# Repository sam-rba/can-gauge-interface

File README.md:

# Analog Gauge Driver with CAN Interface

Automotive electronic device that drives up to six analog gauges using data from a CAN bus.

## Contents

- `hw/` — Hardware; KiCad files for the PCB.
- `fw/` — Firmare that runs on the PIC microcontroller.
- `sw/` — Software for flashing calibration files onto the device.
- `doc/` — Documentation.

## Features

### Interfaces
- CAN 2.0B interface, up to 500kbps
- Flexible CAN encoding scheme, configurable via CAN

### Outputs
- 1 tachometer output
- 1 speedometer output
- 4 analog outputs (0–5V)

### Power supply
- 9–16V DC input

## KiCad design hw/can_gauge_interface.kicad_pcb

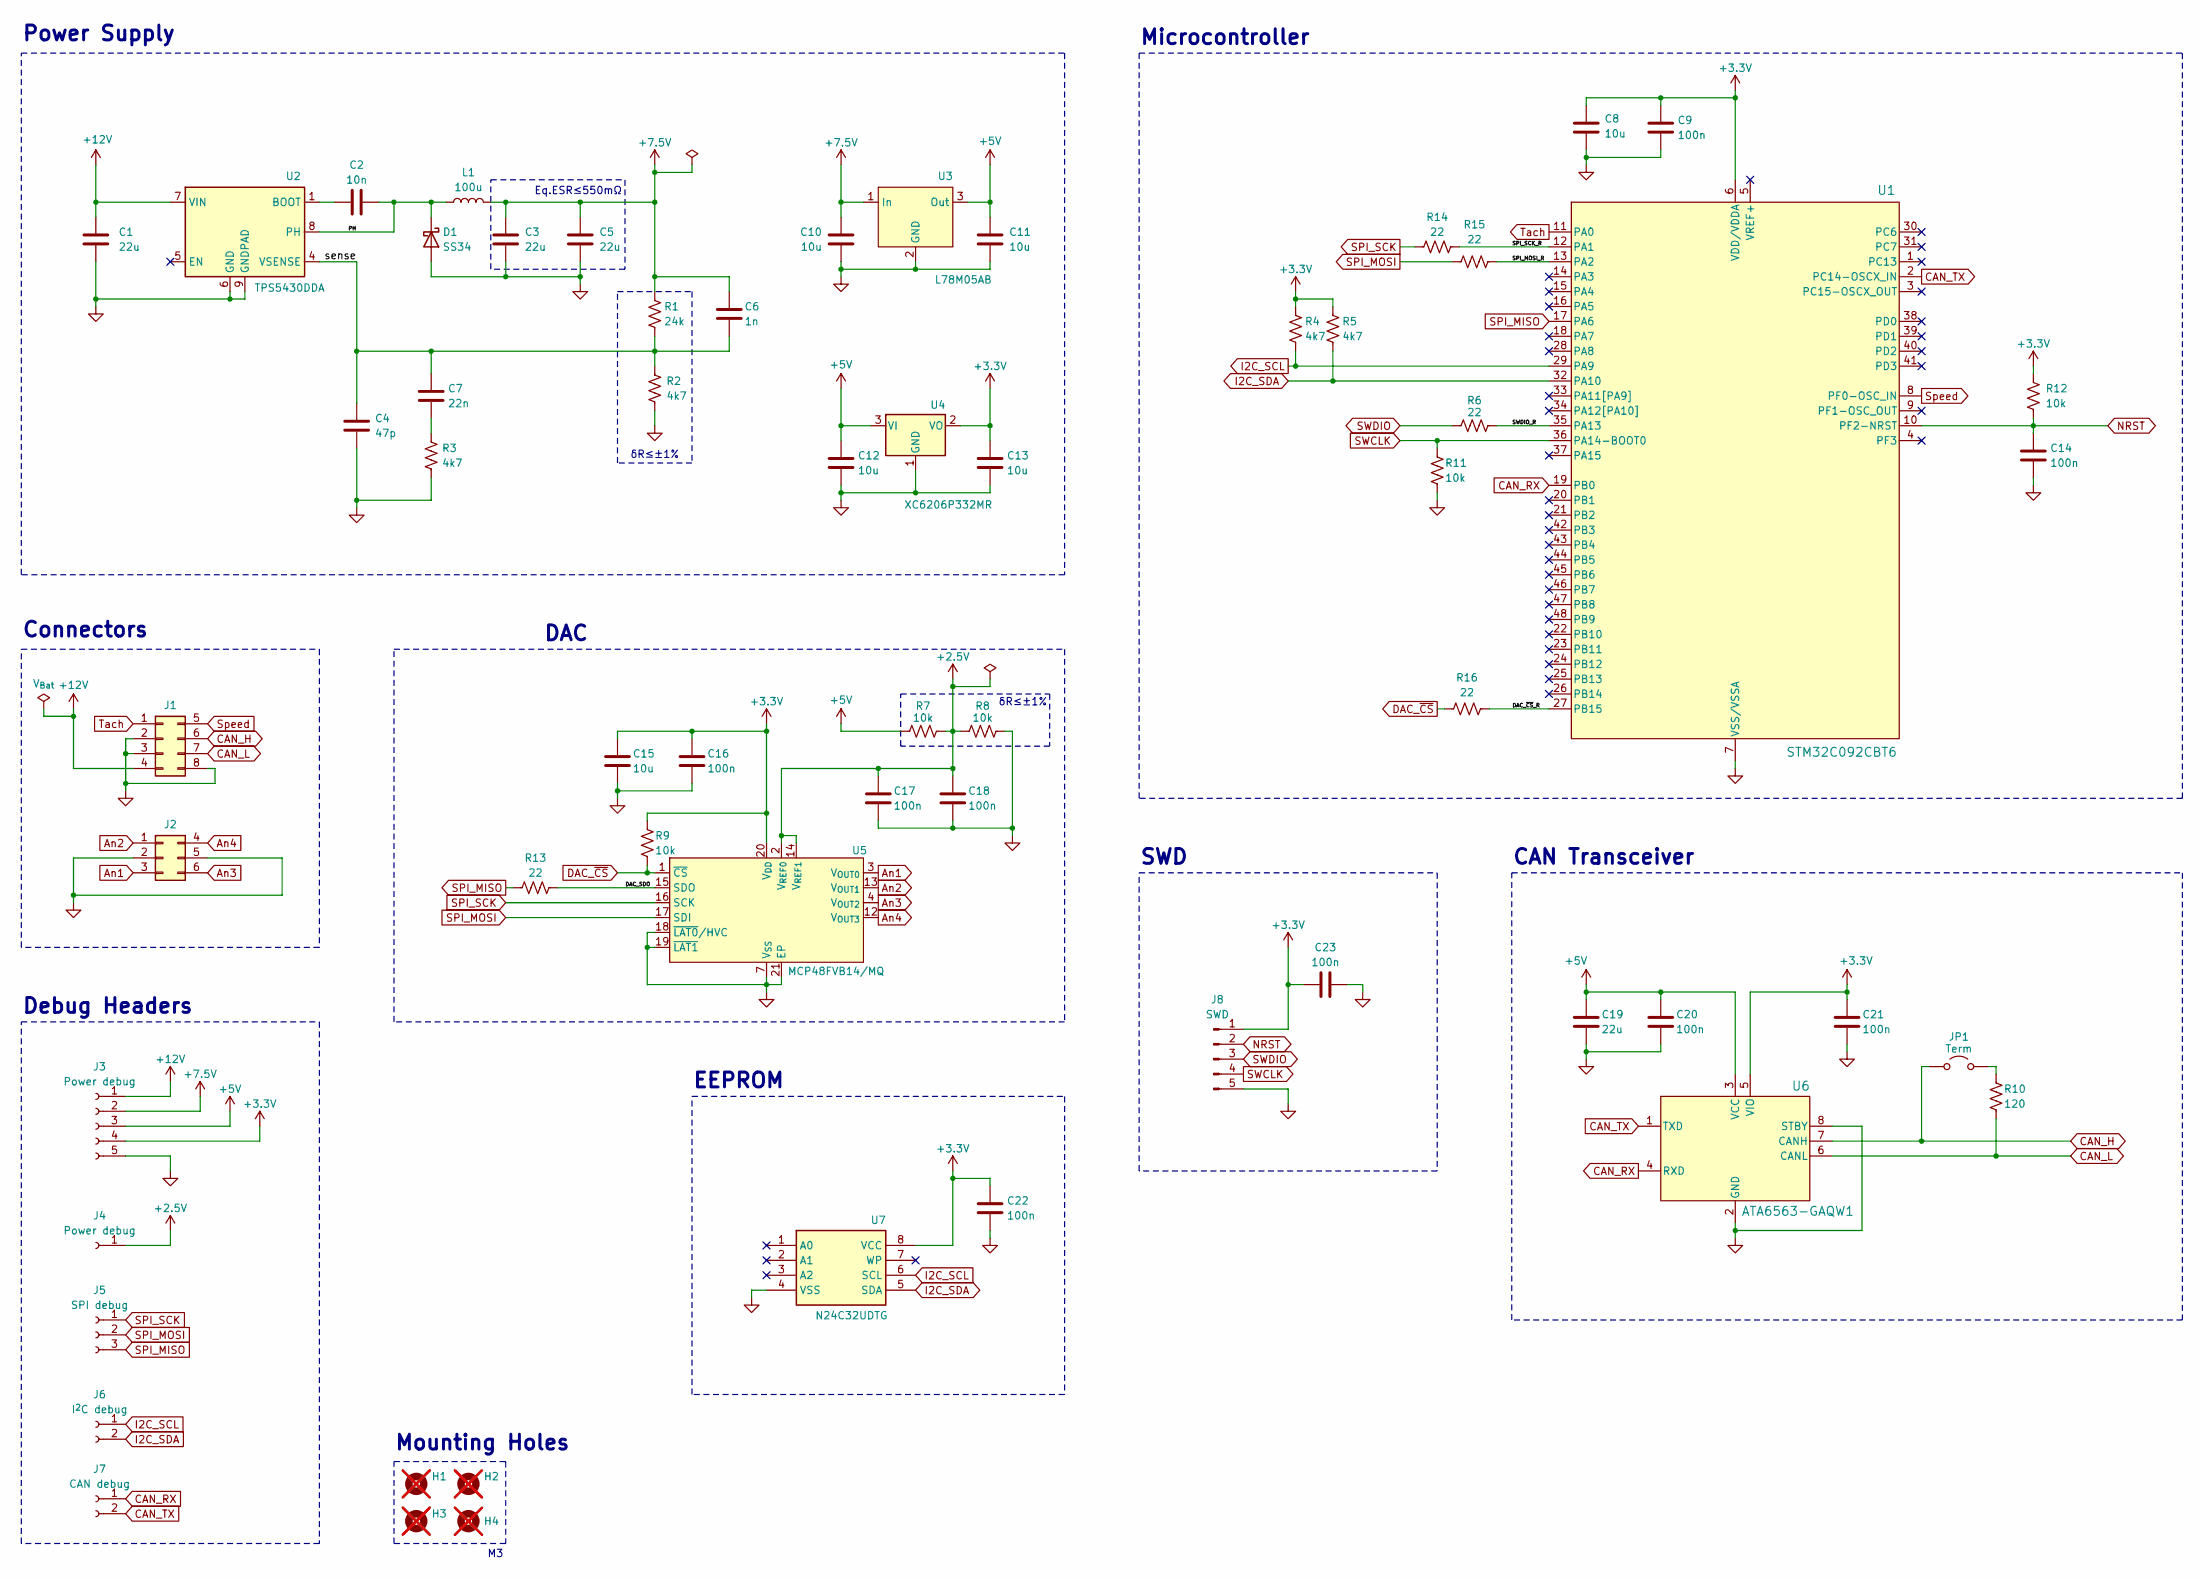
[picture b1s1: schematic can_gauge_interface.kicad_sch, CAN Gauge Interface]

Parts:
C1, C3, C5, C19: 22u; C_1206_3216Metric
C2: 10n; C_0402_1005Metric
C4: 47p; C_0402_1005Metric
C6: 1n; C_0603_1608Metric
C7: 22n; C_0603_1608Metric
C8, C10, C11, C12, C13, C15: 10u; C_0805_2012Metric
C9, C14, C16, C17, C18, C20, C21, C22, C23: 100n; C_0402_1005Metric
D1: SS34; D_SMA
H1, H2, H3, H4: MountingHole; MountingHole_3.2mm_M3_DIN965; not fitted
J1: Conn_02x04_Top_Bottom; Molex_Mini-Fit_Jr_5569-08A2_2x04_P4.20mm_Horizontal
J2: Analog; Molex_Mini-Fit_Jr_5569-06A2_2x03_P4.20mm_Horizontal
J3: Power debug; PinSocket_1x05_P2.54mm_Vertical
J4: Power debug; PinSocket_1x01_P2.54mm_Vertical
J5: SPI debug; PinSocket_1x03_P2.54mm_Vertical
J6: I^{2}C debug; PinSocket_1x02_P2.54mm_Vertical
J7: CAN debug; PinSocket_1x02_P2.54mm_Vertical
J8: SWD; PinHeader_1x05_P2.54mm_Vertical
JP1: Term; TestPoint_2Pads_Pitch2.54mm_Drill0.8mm
L1: 100u; L_TaiTech_TMPC1265_13.5x12.5mm
R1: 24k; R_0603_1608Metric
R2, R3, R4, R5: 4k7; R_0603_1608Metric
R6, R13, R14, R15, R16: 22; R_0603_1608Metric
R7, R8, R9, R11, R12: 10k; R_0603_1608Metric
R10: 120; R_0603_1608Metric
U1: STM32C092CBT6; LQFP48_STM
U2: TPS5430DDA; TI_SO-PowerPAD-8
U3: L78M05AB; TO-252-2
U4: XC6206P332MR; SOT-23-3
U5: MCP48FVB14/MQ; Texas_RGW0020A_VQFN-20-1EP_5x5mm_P0.65mm_EP3.15x3.15mm
U6: ATA6563-GAQW1; SOIC8_SN_MCH
U7: N24C32UDTG; SOP50P312X90-8N; Manufacturer_Part_Number N24C32UDTG; Mouser Part Number 863-N24C32UDTG

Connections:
+2.5V: C17.1, C18.1, J4.1, R7.2, R8.1, U5.2 (V_{REF0}), U5.14 (V_{REF1})
+3.3V: C8.1, C9.1, C13.1, C15.1, C16.1, C21.1, C22.1, C23.1, J3.4, J8.1, R4.1, R5.1, R9.1, R12.1, U1.6 (VDD/VDDA), U4.2 (VO), U5.20 (V_{DD}), U6.5 (VIO), U7.8 (VCC)
+5V: C11.1, C12.1, C19.1, C20.1, J3.3, R7.1, U3.3 (Out), U4.3 (VI), U6.3 (VCC)
+7.5V: C3.1, C5.1, C6.1, C10.1, J3.2, L1.2, R1.1, U3.1 (In)
+12V: C1.1, J1.4, J3.1, U2.7 (VIN)
/DAC_SDO: R13.2, U5.15 (SDO)
/DAC_~CS_R: R16.2, U1.27 (PB15)
/PH: C2.2, D1.1 (K), L1.1, U2.8 (PH)
/SPI_MOSI_R: R15.2, U1.13 (PA2)
/SPI_SCK_R: R14.2, U1.12 (PA1)
/SWDIO_R: R6.2, U1.35 (PA13)
/sense: C4.1, C6.2, C7.1, R1.2, R2.1, U2.4 (VSENSE)
An1: J2.3, U5.3 (V_{OUT0})
An2: J2.1, U5.13 (V_{OUT1})
An3: J2.6, U5.4 (V_{OUT2})
An4: J2.4, U5.12 (V_{OUT3})
CAN_H: J1.6, JP1.1 (A), U6.7 (CANH)
CAN_L: J1.7, R10.2, U6.6 (CANL)
CAN_RX: J7.1, U1.19 (PB0), U6.4 (RXD)
CAN_TX: J7.2, U1.2 (PC14-OSCX_IN), U6.1 (TXD)
DAC_~CS: R9.2, R16.1, U5.1 (~CS)
GND: C1.2, C3.2, C4.2, C5.2, C8.2, C9.2, C10.2, C11.2, C12.2, C13.2, C14.2, C15.2, C16.2, C17.2, C18.2, C19.2, C20.2, C21.2, C22.2, C23.2, D1.2 (A), J1.2, J1.3, J1.8, J2.2, J2.5, J3.5, J8.5, R2.2, R3.2, R8.2, R11.2, U1.7 (VSS/VSSA), U2.6 (GND), U2.9 (GNDPAD), U3.2 (GND), U4.1 (GND), U5.7 (V_{SS}), U5.18 (~LAT0/HVC), U5.19 (~LAT1), U5.21 (EP), U6.2 (GND), U6.8 (STBY), U7.4 (VSS)
I2C_SCL: J6.1, R4.2, U1.29 (PA9), U7.6 (SCL)
I2C_SDA: J6.2, R5.2, U1.32 (PA10), U7.5 (SDA)
NRST: C14.1, J8.2, R12.2, U1.10 (PF2-NRST)
unnamed: C7.2, R3.1
unnamed: JP1.2 (B), R10.1
unnamed: C2.1, U2.1 (BOOT)
SPI_MISO: J5.3, R13.1, U1.17 (PA6)
SPI_MOSI: J5.2, R15.1, U5.17 (SDI)
SPI_SCK: J5.1, R14.1, U5.16 (SCK)
SWCLK: J8.4, R11.1, U1.36 (PA14-BOOT0)
SWDIO: J8.3, R6.1
Speed: J1.5, U1.8 (PF0-OSC_IN)
Tach: J1.1, U1.11 (PA0)

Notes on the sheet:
Connectors
Microcontroller
Power Supply
Eq.ESR≤550mΩ
δR≤±1%
DAC
SWD
Mounting Holes
CAN Transceiver
Debug Headers
EEPROM

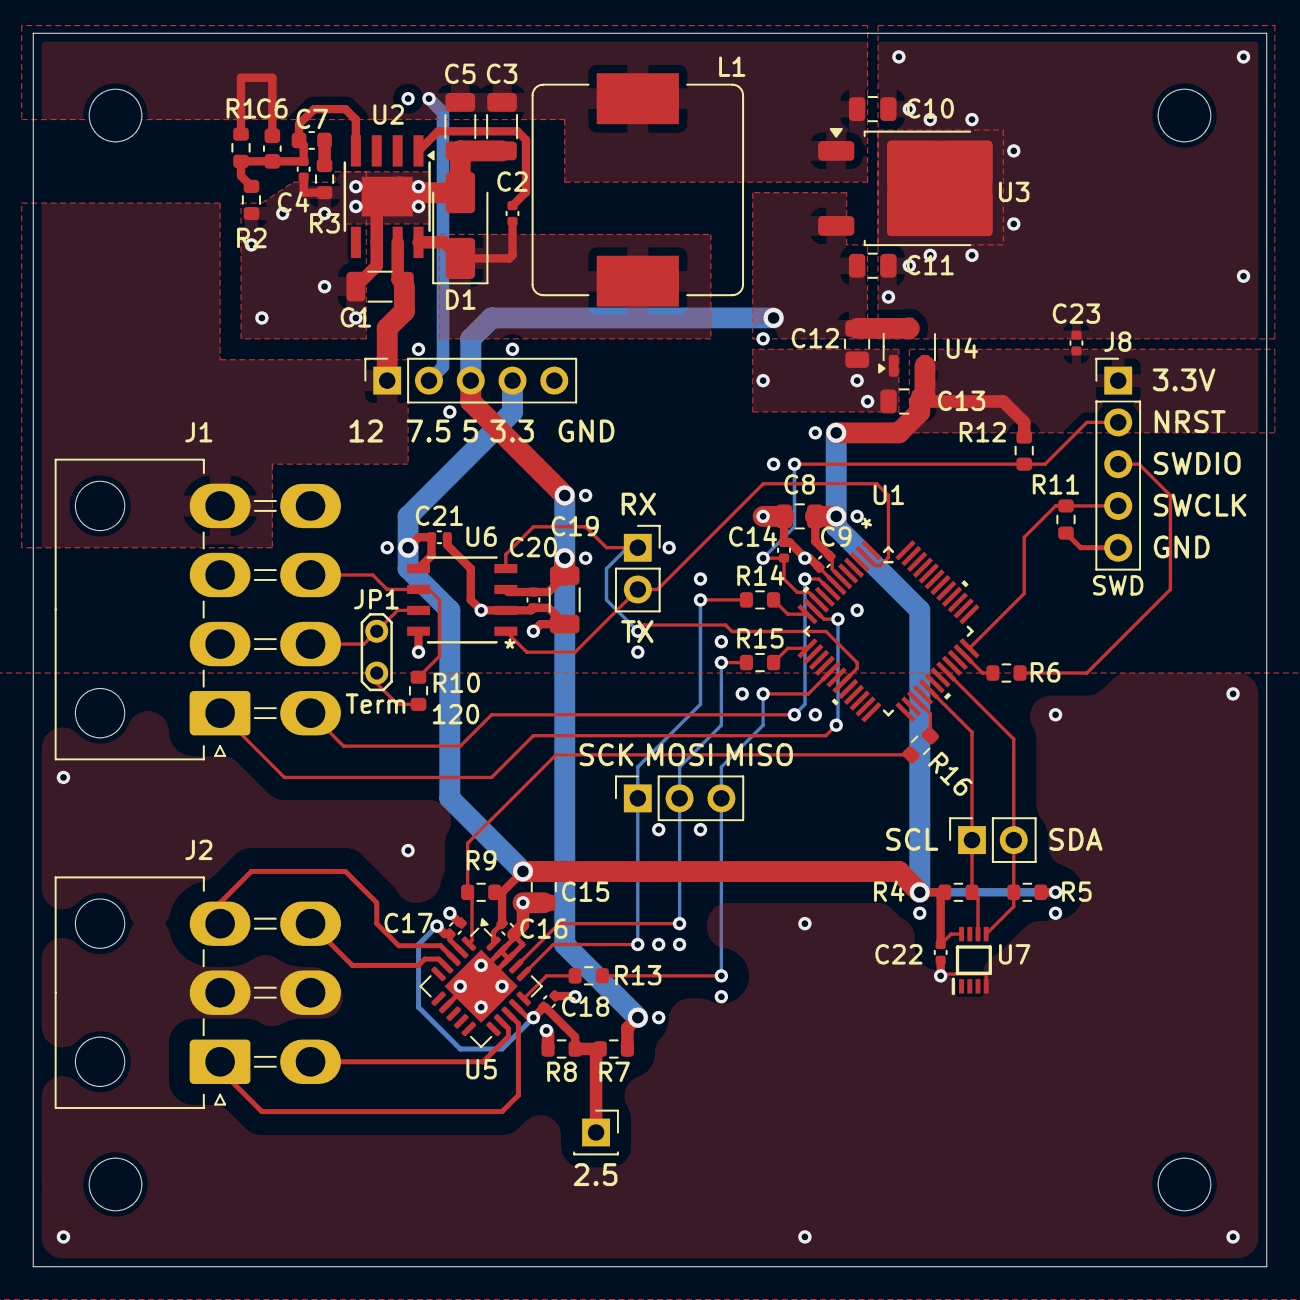
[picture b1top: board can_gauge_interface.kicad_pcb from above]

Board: 4 copper layers, 75.0 x 75.0 mm, 61 parts (0 on the bottom side), 35 nets.

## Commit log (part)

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2025-07-23 proposal
2025-07-24 spelling
2025-08-03 makefile and main.c
2025-08-14 usb protocol
2025-08-16 spi and eeprom modules
2025-08-16 add device and compiler to header comments
2025-08-16 add systests to makefile
2025-08-16 usbcom: modified libusb example
2025-08-16 clean up usbcom
2025-09-02 update proposal
2025-09-04 mla_usb submodule
2025-09-04 fw: usb
2025-09-05 debug usb
2025-09-05 rework usb state machine
2025-09-05 fix bug in usbcom
2025-09-05 usb: preemptive bug fix
2025-09-05 usb: add nack to protocol
2025-09-06 unity submodule
2025-09-06 usb getchar()
2025-09-06 fw: handle "w" write eeprom command
2025-09-06 fw: handle "r" eeprom read command
2025-09-06 make microchip source files non-executable
2025-09-06 tach/speedo discussion
2025-09-07 power budget
2025-09-07 power supply schematic
2025-09-07 schematic: MCLR, USB, ICSP
2025-09-07 schematic: EEPROM
2025-09-07 schematic: CAN
2025-09-08 schematic: connectors
2025-09-08 schematic: spi debug header
2025-09-08 more debug headers
2025-09-08 schematic: CAN termination jumper
2025-09-17 usbcom go rewrite
2025-09-17 usbcom refactor
2025-09-17 bug fix: eeprom usb newline
2025-09-19 hw: digital and analog LDOs
2025-09-19 hw: 6v6 debug pin
2025-09-19 hw: connected pic gpios
2025-09-19 hw: fixed erc warnings
2025-09-19 footprints
2025-09-20 buck converter layout and routing
2025-09-20 analog ldo layout and routing
2025-09-20 analog routing
2025-09-20 digital ldo layout and routing
2025-09-20 tht decoupling caps
2025-09-20 layout
2025-09-20 dac pullup layout
2025-09-20 4 layer stackup and CAN routing
2025-09-20 spi routing
2025-09-20 int pin routing
2025-09-20 CAN_CS routing
2025-09-20 icsp routing
2025-09-20 usb data routing
2025-09-20 speed and tach routing
2025-09-20 connected buck to conn pin
2025-09-20 dac spi routing
2025-09-20 move sck away from analog
2025-09-20 mounting hole placement
2025-09-20 edge cuts
2025-09-22 moved analog
2025-09-22 gnd vias
2025-09-22 drc warnings
2025-09-22 gnd pours
2025-09-27 psu ic 3d models
2025-09-27 tht quote
2025-09-27 schematic: tps5430 buck
2025-09-27 schematic: ldos
2025-09-27 schemtic: removed DNP flags
2025-09-27 wurth usb connector symbol
2025-09-27 board setup
2025-09-27 buck layout
2025-09-27 ldo layout
2025-09-27 can layout
2025-09-28 pic layout
2025-09-29 tht passives
2025-09-29 buck routing
2025-09-29 routing
2025-09-29 more routing
2025-09-29 wash
2025-10-01 tune usb trace length
2025-10-01 removed usb vbus
2025-10-01 manufacturing files
2025-10-01 connector 3d models
2025-10-02 manufacturing
2025-10-02 spi systest
2025-10-02 dac fw module
2025-10-03 CAN bit timing
2025-10-03 mcp2515 spi functions
2025-10-04 fix bug in bittiming script
2025-10-04 CAN filter- and mask-setting functions
2025-10-13 midterm report: intro and desiderata
2025-10-13 midterm report: component selection
2025-10-13 midterm report: pcb design
2025-10-13 midterm report: firmware
2025-10-13 midterm report: next steps
2025-10-13 midterm report: wash
2025-10-14 remove deprecated power supply doc
2025-10-14 remove old usbcom makefile
2025-10-14 reduce size of image
2025-10-15 usbtin bed and standoff models
2025-10-15 move hw/ back to top level
2025-10-23 board for bed
2025-10-23 recalculate bittimings
2025-10-23 canTx()
2025-10-23 can tx systest
2025-10-23 fw: remove usb
2025-10-23 enable CLKOUT
2025-10-24 CAN echo systest
2025-10-24 eeprom systest
2025-10-24 table module
2025-10-25 CAN frame format doc
2025-10-25 remove old USB protocol doc
2025-10-25 read/write CAN ID in EEPROM
2025-10-25 load CAN IDs from EEPROM
2025-10-25 handle ID Control Frames
2025-10-25 fix CAN ID format
2025-10-27 add unit tests to makefile
2025-10-27 handle ID Control frames (wip)
2025-10-28 use builtin int types
2025-11-01 update systests
2025-11-01 update datafmt doc
2025-11-01 rename parameter->signal to align with DBC standard
2025-11-01 serialization module
2025-11-01 extract big-endian signals from frames
2025-11-01 main signal processing stubs
2025-11-01 extract little-endian signals from frames
2025-11-01 remove xc.h from modules that don't need it
2025-11-01 fix compiler warnings
2025-11-01 extract signal from received frames
2025-11-02 lookup output value in table
2025-11-07 respond to Signal Control REMOTE FRAME
2025-11-07 handle Signal Control DATA FRAME
2025-11-07 fix bug in CAN ID packing
2025-11-07 transmit line number on error
2025-11-07 SigFmt serialization functions
2025-11-07 remove debugging code
2025-11-07 handle Table Control frame
2025-11-07 int serialization functions
2025-11-07 cal: parse dbc file
2025-11-07 cal: parse dbc signals
2025-11-07 cal: refactor
2025-11-07 cal: parse csv tables
2025-11-08 cal: transmit table to CAN bus
2025-11-08 cal: retransmit on buffer full error
2025-11-08 cal: wash
2025-11-08 cal: send Signal Control framess
2025-11-08 swap signal byte_order to reflect amended dbc spec
2025-11-08 specify dac voltage in millivolts
2025-11-08 can: fix bug in packID(); add retry delay
2025-11-08 debugging
2025-11-08 cal: add delay between transmissions to let eeprom write
2025-11-08 fix table lookup
2025-11-08 limit table keys to i32; add table linear interpolation
2025-11-08 update table.h comment
2025-11-08 cal: verify signal encoding after writing
2025-11-09 cal: verify table after writing
2025-11-10 cal: cleanup flags
2025-11-10 generate tachometer signal
2025-11-10 disable tachometer output below min threshold
2025-11-10 generate speedometer signal
2025-11-10 use short register names
2025-11-10 increase spi clock rate to 3MHz
2025-11-17 add license
2025-12-08 move proposal and midterm report to doc/
2025-12-08 report: outline
2025-12-08 report: start introduction
2025-12-09 report: boeing and r31 figures, editing
2025-12-09 report: introduction
2025-12-10 report: project overview
2025-12-10 report: block diagram
2025-12-13 report: timeline
2025-12-13 report: hardware component selection
2025-12-13 report: power supply
2025-12-13 report: pcb design
2025-12-13 report: firmware
2025-12-13 report: firmware module dependency graph
2025-12-13 rename datafmt doc to calfmt
2025-12-13 report: calibration
2025-12-13 remove usbcom
2025-12-15 report: bit timing
2025-12-15 report: calibration software
2025-12-15 cal: example dbc and csv files
2025-12-15 report: testing
2025-12-15 report: conclusion
2025-12-15 report: abstract
2025-12-15 report: spelling
2025-12-15 report: pdn diagram
2025-12-16 report: editing
2025-12-16 report: add date
2025-12-27 ATA6563, N24C32, and STM32C092 symbols
2025-12-27 schematic: rework with stm32c092
2025-12-27 schematic: debug headers; annotate
2025-12-27 schematic: erc
2025-12-27 schematic: assign IC footprints
2025-12-27 schematic: assign footprints
2025-12-28 pcb: buck converter layout
2025-12-28 pcb: ldo layout
2025-12-29 schematic: mcu pinout
2025-12-29 schematic: swd
2025-12-30 schematic: use generic header for swd
2025-12-30 schematic: spi termination resistors
2025-12-30 pcb: fix buck layout
2025-12-30 pcb: CAN transceiver layout
2025-12-30 pcb: dac layout
2025-12-30 pcb: mcu layout
2025-12-30 pcb: eeprom layout
2025-12-31 pcb: layout
2025-12-31 pcb: buck routing
2025-12-31 pcb: spi routing
2025-12-31 pcb: CAN transceiver routing
2025-12-31 pcb: ldo routing
2025-12-31 pcb: CAN routing
2025-12-31 pcb: dac routing
2025-12-31 pcb: eeprom routing
2025-12-31 pcb: signal routing
2025-12-31 pcb: swd routing
2025-12-31 pcb: 3v3 routing
2025-12-31 pcb: 5v routing
2025-12-31 pcb: drc
2026-01-01 pcb: more drc
2026-01-01 pcb: clean up routing
2026-01-01 pcb: gnd pour
2026-01-01 pcb: spi debug header labels
2026-01-15 compile report
2026-01-15 report makefile
2026-01-15 readme: add features section
2026-02-07 hw: microcontroller hierarchical sheet
2026-02-07 hw: clean up microcontroller schematic
2026-02-07 hw: power supply hierarchical sheets
2026-02-07 connectors hierarchical sheet
2026-02-07 hw: dac hierarchical sheet
2026-02-07 hw: eeprom hierarchical sheet
2026-02-07 hw: can transceiver hierarchical sheet
2026-02-07 hw: headers hierarchical sheet
2026-02-07 hw: top level schematic
2026-02-07 hw: output bus
2026-02-07 hw: erc: can
2026-02-07 hw: erc: power
2026-02-07 hw: clean up schematic
2026-04-21 hw: add American Embedded build script
